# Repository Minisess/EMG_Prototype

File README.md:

# EMG_Prototype
A simple two electrode EMG from scratch
I designed this as a challenge to myself. I am a student of Biochemistry and I want to study 
brain computer interfaces. As a resut learning the circuitry and many varied tools that 
are involved in circuit design and electronics is up to me at the present.

This project was a study of operational amplifiers as well as the nature of myo-electric signals. 
It utilizes an Instrumental Amp for signal aquisition and a dual op-amp for a first order band pass filter 
at about 10Hz to 500Hz.

I am currently working on more software that can add application and utility to signal processing.

Connections:
This project is intended for use with an Arduino over a Serial connection at present. 
Though the pin pairs of labeled intention is that 

Power: 
Power would supply a 5V potential across the two pins from an external power supply.

Electrodes:
The center four pins are intended to be used with three electrodes with the last pin being
a ground for the purpose of shielding in the wires. 

Voltage Read:
Last the Voltage read pins will go into the Arduino GND and A0

Suggestions are welcome and feel free to contact me at

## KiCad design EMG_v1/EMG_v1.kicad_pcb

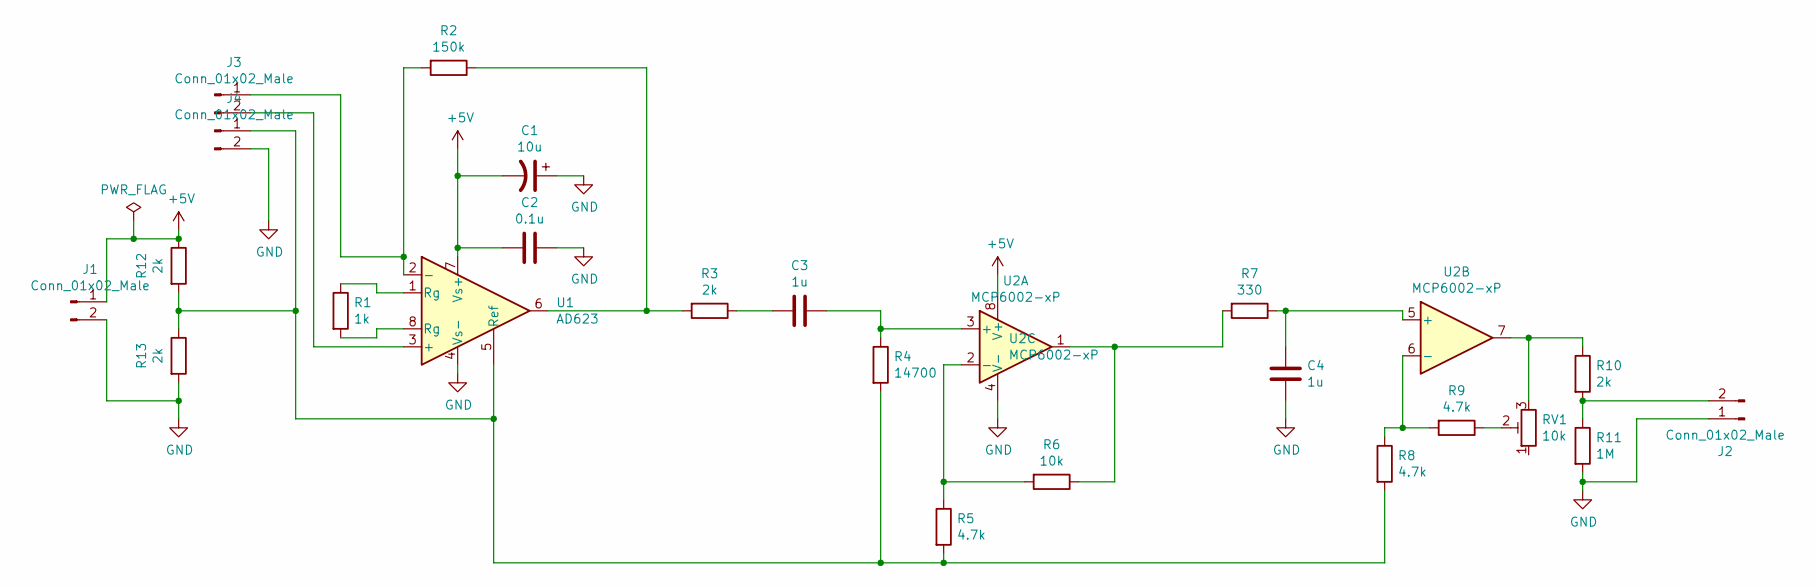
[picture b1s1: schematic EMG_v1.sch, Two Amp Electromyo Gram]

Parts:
C1: 10u; CP_Radial_D5.0mm_P2.00mm
C2: 0.1u; C_0402_1005Metric
C3, C4: 1u; C_0603_1608Metric
J1, J2, J3, J4: Conn_01x02_Male; Terminal_Block_D1.3mm_P5mm
R1: 1k; R_Axial_DIN0207_L6.3mm_D2.5mm_P7.62mm_Horizontal
R2: 150k; R_Axial_DIN0207_L6.3mm_D2.5mm_P7.62mm_Horizontal
R3, R10, R12, R13: 2k; R_Axial_DIN0207_L6.3mm_D2.5mm_P7.62mm_Horizontal
R4: 14700; R_Axial_DIN0207_L6.3mm_D2.5mm_P7.62mm_Horizontal
R5, R8, R9: 4.7k; R_Axial_DIN0207_L6.3mm_D2.5mm_P7.62mm_Horizontal
R6: 10k; R_Axial_DIN0207_L6.3mm_D2.5mm_P7.62mm_Horizontal
R7: 330; R_Axial_DIN0207_L6.3mm_D2.5mm_P7.62mm_Horizontal
R11: 1M; R_Axial_DIN0207_L6.3mm_D2.5mm_P7.62mm_Horizontal
RV1: 10k; Potentiometer_Bourns_3296W_Vertical
U1: AD623; SOCKET_DIP-8_7.62mm_Conn
U2: MCP6002-xP; SOCKET_DIP-8_7.62mm_Conn

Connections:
+5V: C1.2, C2.2, J1.1, R12.1, U1.7 (Vs+), U2.8 (V+)
GND: C1.1, C2.1, C4.2, J1.2, J2.1, J4.2, R11.2, R13.2, U1.4 (Vs-), U2.4 (V-)
unnamed: C3.1, R4.1, U2.3 (+)
unnamed: C3.2, R3.1
unnamed: C4.1, R7.1, U2.5 (+)
unnamed: J2.2, R10.2, R11.1
unnamed: J3.1, R2.2, U1.2 (-)
unnamed: J3.2, U1.3 (+)
unnamed: J4.1, R4.2, R5.2, R8.2, R12.2, R13.1, U1.5 (Ref)
unnamed: R1.1, U1.1 (Rg)
unnamed: R1.2, U1.8 (Rg)
unnamed: R2.1, R3.2, U1.6
unnamed: R5.1, R6.2, U2.2 (-)
unnamed: R6.1, R7.2, U2.1
unnamed: R8.1, R9.2, U2.6 (-)
unnamed: R9.1, RV1.2
unnamed: R10.1, RV1.3, U2.7

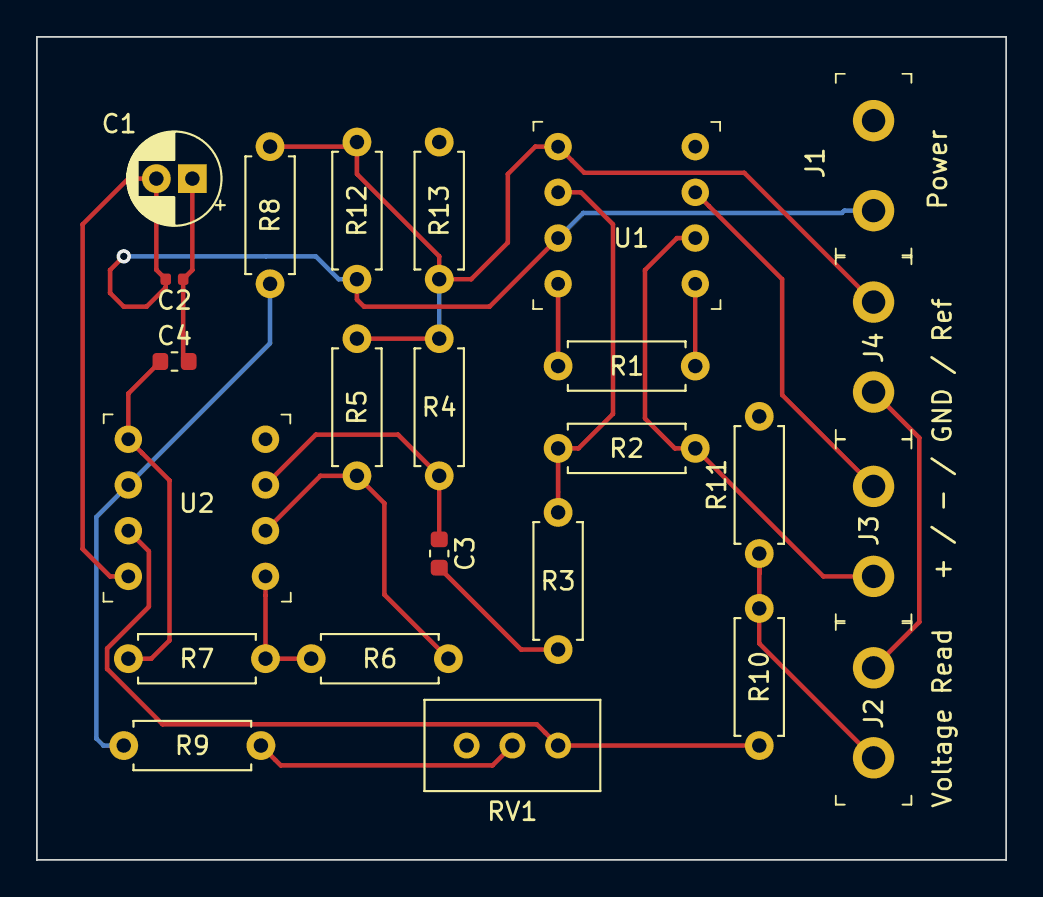
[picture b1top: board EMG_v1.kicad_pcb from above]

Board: 2 copper layers, 53.8 x 45.7 mm, 24 parts (0 on the bottom side), 17 nets.
